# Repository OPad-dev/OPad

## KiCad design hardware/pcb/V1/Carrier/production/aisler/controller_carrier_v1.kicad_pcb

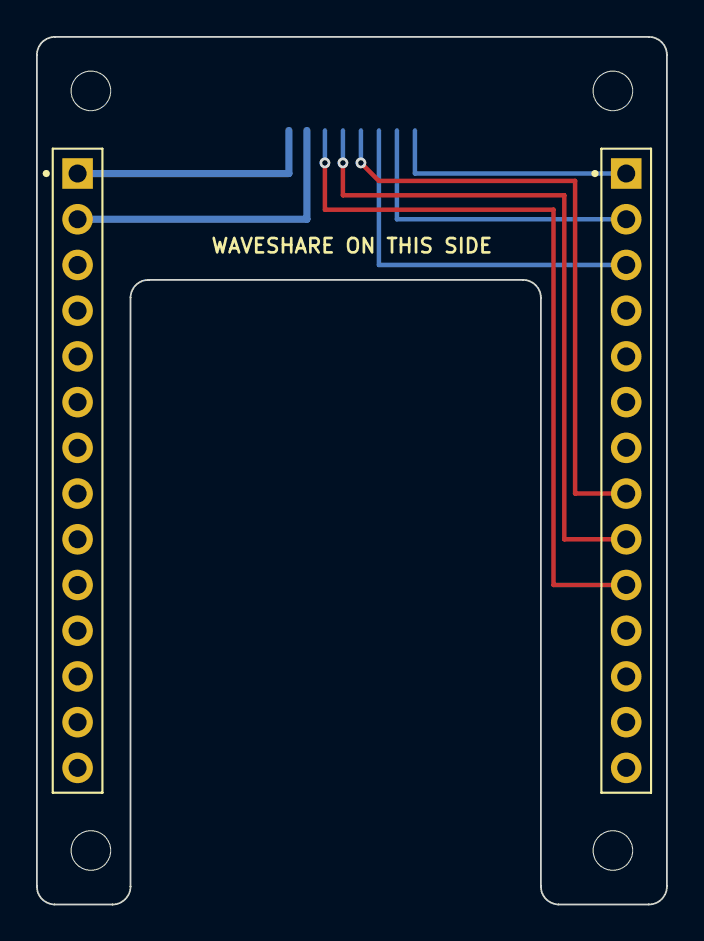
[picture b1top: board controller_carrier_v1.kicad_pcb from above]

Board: 2 copper layers, 35.0 x 48.2 mm, 7 parts (1 on the bottom side), 8 nets.

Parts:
H1, H2, H3, H4: MountingHole_2.2mm_M2
J_MOD: MODULE; JST_SH_SM08B-SRSS-TB_1x08-1MP_P1.00mm_Horizontal
J_P1: WAVESHARE_P1; PinSocket_1x14_P2.54mm_Vertical
J_P2: WAVESHARE_P2; PinSocket_1x14_P2.54mm_Vertical

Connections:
/3V3: J_MOD.1, J_P2.1
/GND: J_MOD.2, J_P2.2
/ID: J_MOD.5, J_P1.8
/IN1: J_MOD.3, J_P1.10
/IN2: J_MOD.4, J_P1.9
/IO2: J_MOD.8, J_P1.1
/IO4: J_MOD.7, J_P1.2
/IO6: J_MOD.6, J_P1.3

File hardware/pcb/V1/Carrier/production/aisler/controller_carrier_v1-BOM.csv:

Reference,Quantity,Value,Footprint,MFG,MPN,LCSC,Side,Type
"J_P2",1,WAVESHARE_P2,PinSocket_1x14_P2.54mm_Vertical,HCTL,PM254-1-14-Z-8.5,C2897377,top,THT
"J_P1",1,WAVESHARE_P1,PinSocket_1x14_P2.54mm_Vertical,HCTL,PM254-1-14-Z-8.5,C2897377,top,THT
"J_MOD",1,MODULE,JST_SH_SM08B-SRSS-TB_1x08-1MP_P1.00mm_Horizontal,JST,SM08B-SRSS-TB(LF)(SN),C160407,bottom,SMD

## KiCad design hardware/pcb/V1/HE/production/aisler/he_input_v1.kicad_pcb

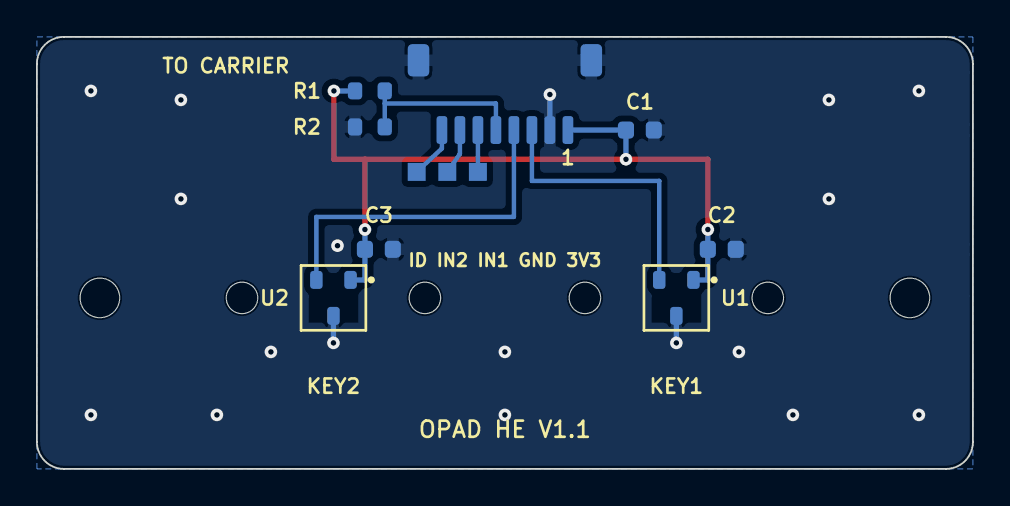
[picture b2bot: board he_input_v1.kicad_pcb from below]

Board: 2 copper layers, 52.0 x 24.0 mm, 15 parts (13 on the bottom side), 8 nets.

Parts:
C1, C2, C3: 100nF; C_0603_1608Metric
H1, H2: MountingHole_2.2mm_M2
J1: MODULE; JST_SH_SM08B-SRSS-TB_1x08-1MP_P1.00mm_Horizontal
R1: 100k; R_0603_1608Metric
R2: 47k; R_0603_1608Metric
SW1: KEY1; SW_MX_Hall_PlateMount_SolidCentre
SW2: KEY2; SW_MX_Hall_PlateMount_SolidCentre
TP1: IO6; TestPoint_Pad_1.0x1.0mm
TP2: IO4; TestPoint_Pad_1.0x1.0mm
TP3: IO2; TestPoint_Pad_1.0x1.0mm
U1, U2: DRV5055A3; SOT-23

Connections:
/3V3: C1.2, C2.2, C3.2, J1.1, R1.2, U1.1, U2.1
/GND: C1.1, C2.1, C3.1, J1.2, J1.MP, R2.2, U1.3, U2.3
/ID: J1.5, R1.1, R2.1
/IN1: J1.3, U1.2
/IN2: J1.4, U2.2
/IO2: J1.8, TP3.1
/IO4: J1.7, TP2.1
/IO6: J1.6, TP1.1

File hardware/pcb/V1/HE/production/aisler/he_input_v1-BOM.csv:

Reference,Quantity,Value,Footprint,MFG,MPN,LCSC,Side,Type
"U1,U2",2,DRV5055A3,SOT-23,Texas Instruments,DRV5055A3QDBZR,C266128,bottom,SMD
"C2,C3,C1",3,100nF,C_0603_1608Metric,YAGEO,CC0603KRX7R9BB104,C14663,bottom,SMD
"J1",1,MODULE,JST_SH_SM08B-SRSS-TB_1x08-1MP_P1.00mm_Horizontal,JST,SM08B-SRSS-TB(LF)(SN),C160407,bottom,SMD
"R1",1,100k,R_0603_1608Metric,UNI-ROYAL,0603WAF1003T5E,C25803,bottom,SMD
"R2",1,47k,R_0603_1608Metric,UNI-ROYAL,0603WAF4702T5E,C25819,bottom,SMD

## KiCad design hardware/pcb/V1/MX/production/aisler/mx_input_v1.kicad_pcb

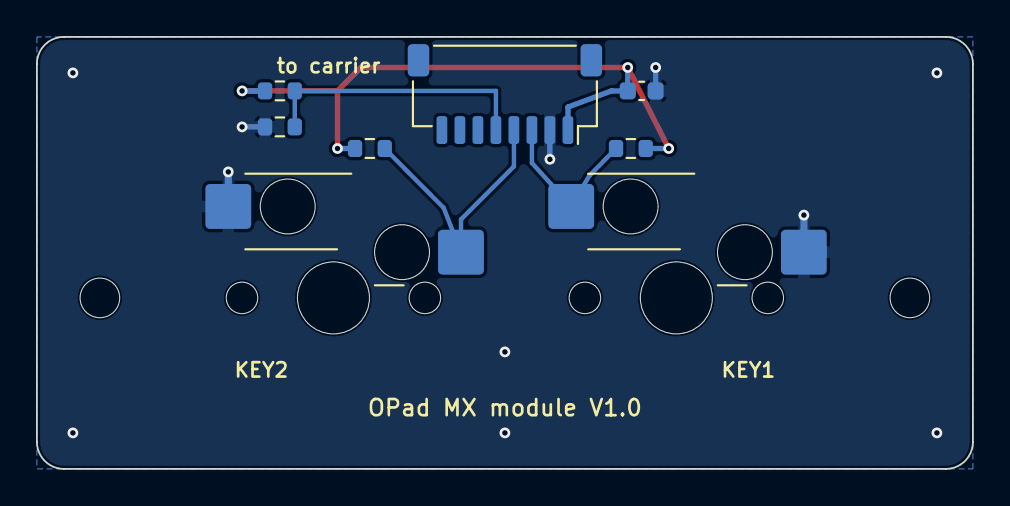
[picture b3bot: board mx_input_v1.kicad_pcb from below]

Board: 2 copper layers, 52.0 x 24.0 mm, 10 parts (8 on the bottom side), 5 nets.

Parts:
C1: 100nF; C_0603_1608Metric
H1, H2: MountingHole_2.2mm_M2
J1: MODULE; JST_SH_SM08B-SRSS-TB_1x08-1MP_P1.00mm_Horizontal
R1, R2, R4: 10k; R_0603_1608Metric
R3: 100k; R_0603_1608Metric
SW1: KEY1; Kailh_CPG151101S11_MX_Hotswap_Bottom
SW2: KEY2; Kailh_CPG151101S11_MX_Hotswap_Bottom

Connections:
/3V3: C1.2, J1.1, R1.1, R2.2, R3.2
/GND: C1.1, J1.2, R4.2, SW1.1, SW2.2
/ID: J1.5, R3.1, R4.1
/IN1: J1.3, R1.2, SW1.2
/IN2: J1.4, R2.1, SW2.1

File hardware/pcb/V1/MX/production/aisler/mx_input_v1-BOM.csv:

Reference,Quantity,Value,Footprint,MFG,MPN,LCSC,Side,Type
"R1,R2,R4",3,10k,R_0603_1608Metric,UNI-ROYAL,0603WAF1002T5E,C25804,bottom,SMD
"C1",1,100nF,C_0603_1608Metric,YAGEO,CC0603KRX7R9BB104,C14663,bottom,SMD
"J1",1,MODULE,JST_SH_SM08B-SRSS-TB_1x08-1MP_P1.00mm_Horizontal,JST,SM08B-SRSS-TB(LF)(SN),C160407,bottom,SMD
"R3",1,100k,R_0603_1608Metric,UNI-ROYAL,0603WAF1003T5E,C25803,bottom,SMD
"SW2",1,KEY2,Kailh_CPG151101S11_MX_Hotswap_Bottom,Kailh,CPG151101S11,C41430893,bottom,SMD
"SW1",1,KEY1,Kailh_CPG151101S11_MX_Hotswap_Bottom,Kailh,CPG151101S11,C41430893,bottom,SMD
